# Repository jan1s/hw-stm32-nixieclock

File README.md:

# hw-nixieclock

The firmware running on the clock: [Firmware](https://github.com/jan1s/fw-clock)

A small Gist to configure a STM32 toolchain on Mac: [Toolchain](https://jan1s.github.io)

To flash the controller a STM32 Programmer is needed, just get the cheapest one from China.

## Initial Configuration

Before the clock will actually start working, it is necessary to set the type:

```bash
nixie_settype <type>
nixie_settype <type(0-4)>
```

Where `<type>` is a number defining the nixie clock type.

1. ZM1000
2. Z570M, IN-8
3. ZM1325
4. IN-14, ZM1020

It is also required to set the mode of operation:

```bash
nixie_setmode <mode>
nixie_setmode <mode(0=NONE|1=HHMMSS|2=HHMM|3=MMSS|4=YYYY)>
```

Where `<mode>` is a number defining the nixie operation mode.

1. HH:MM:SS
2. HH:MM
3. MM:SS
4. YYYY

## PCBs

The clock has seperate control and display pcbs. Those pcbs do not only form a basic case for the electronics, but also allow for flexible use with different tubes.

[Control PCBs](layout/control)

[Display PCBs](layout/display)

[Source PCBs](layout/source)

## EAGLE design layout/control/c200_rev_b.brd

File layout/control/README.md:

# Control PCBs

## c100

rev. a

In the first revision of the PCBs are some minor errors. (This is the version from the 32C3 workshop)
Find detailed pictures of the first prototype [here](../../docu/detail_c100_rev_a).

* A pullup resistor is missing on the USB data lines
* LED silkscreen missing, they are on the right of the controller

rev. b

## c150

rev. a

### control BOM
| Identifier | Type/Value | Quantity | [Reichelt][reichelt] | [Digikey][digikey] | Comment |
| :---        | :---        | :---      | :---         | :---      | :---     |
| R1, R2, R3, R4 | 33 Ω | 4 | SMD-0603 33 | 311-33GRCT-ND |
| R12, R13 | 1 kΩ | 2 | SMD-0603 1,00K | 311-1.0KGRCT-ND |
| C1, C2, C13, C14 | 10 pF | 4 | NPO-G0603 10P |  |
| C7, C8 | 10 nF | 2 | X7R-G0603 10N |  |
| C18, C19, C20, C21 | 100 nF | 4 | X7R-G0603 100N |  |
| C3, C5, C6, C10, C11 | 10 µF | 5 | X5R-G0603 10/6 |  |
| FB1 | Ferrite Bead | 1 | BLM18AG 121 | 490-1011-1-ND |
| Y1 | 8MHz | 1 | - | 535-10630-1-ND |
| Y2 | 32kHz | 1 | 32,768 PGD-9 | 535-9542-1-ND |
| LED1 | LED green | 1 | LG L29K |  |
| LED2 | LED white | 1 | LW L283 | |
| BAT1 | Batteryholder | 1 | - | BC501SM-ND | c100 |
| BAT1 | Batteryholder | 1 | KZH 20SMD-2 | - | c150 |
| BAT | CR 1220 | 1 | CR 1220 VAR | SY033-ND |
| SW1 | Tact Switch Top | 1 | - | EG2531CT-ND |
| J1 | 2x5 Socket | 1 | - | A100866TR-ND, S5714-ND |
| J2 | USB Jack | 1 | USB BWM SMD | 151-1206-1-ND |
| IC1 | STM32F103C8T6 | 1 | STM32 F103C8T6 | 497-6063-ND |
| IC2, IC6 | LP2985 | 1 | LP 2985 IM5-3,3 |  |
| IC3, IC4 | USBLC6-2 | 1 | - | 497-5235-1-ND |

### power supply BOM
| Identifier | Type/Value | Quantity | [Reichelt][reichelt] | [Digikey][digikey] | Comment |
| ---        | ---        | ---      | ---         | ---      | ---     |
| R23 | 0.01 Ω | 1 | - | RHM.10MCT-ND |
| R18 | 82 kΩ | 1 | SMD-0603 82K |  |
| R20 | 8,2 kΩ | 1 | SMD-0603 8,2K |  |
| R19 | 1 MΩ | 1 | SMD-1206 1M |  |
| C12 | 150 pF | 1 | NPO-G0603 150P |  |
| C9 | 22 nF | 1 | X7R-G0603 22N |  |
| C4 | 1 µF / 250V | 1 | 1u/250V | 490-3550-1-ND  | |
| C15, C16 | 10 µF | 2 | X5R-G0603 10/6 |  |
| C17 | 100 µF | 1 | X5R-G1210 100 |  |
| D2 | Diode | 1 | BAT 54C SMD |  |
| D3 | Diode | 1 | ES 2GA SMD |  |
| L2 | 680 µH | 1 | L-PISR 680µ |  |
| IC7 | IRF 7470 | 1 | IRF 7470 | IRF7470PBFCT-ND |
| IC5 | LT1619ES8 | 1 | - | LT1619ES8#PBF-ND |

[reichelt]: http://www.reichelt.de
[digikey]: http://www.digikey.de
[mouser]: http://mouser.com
[aliexpress]: http://www.aliexpress.com

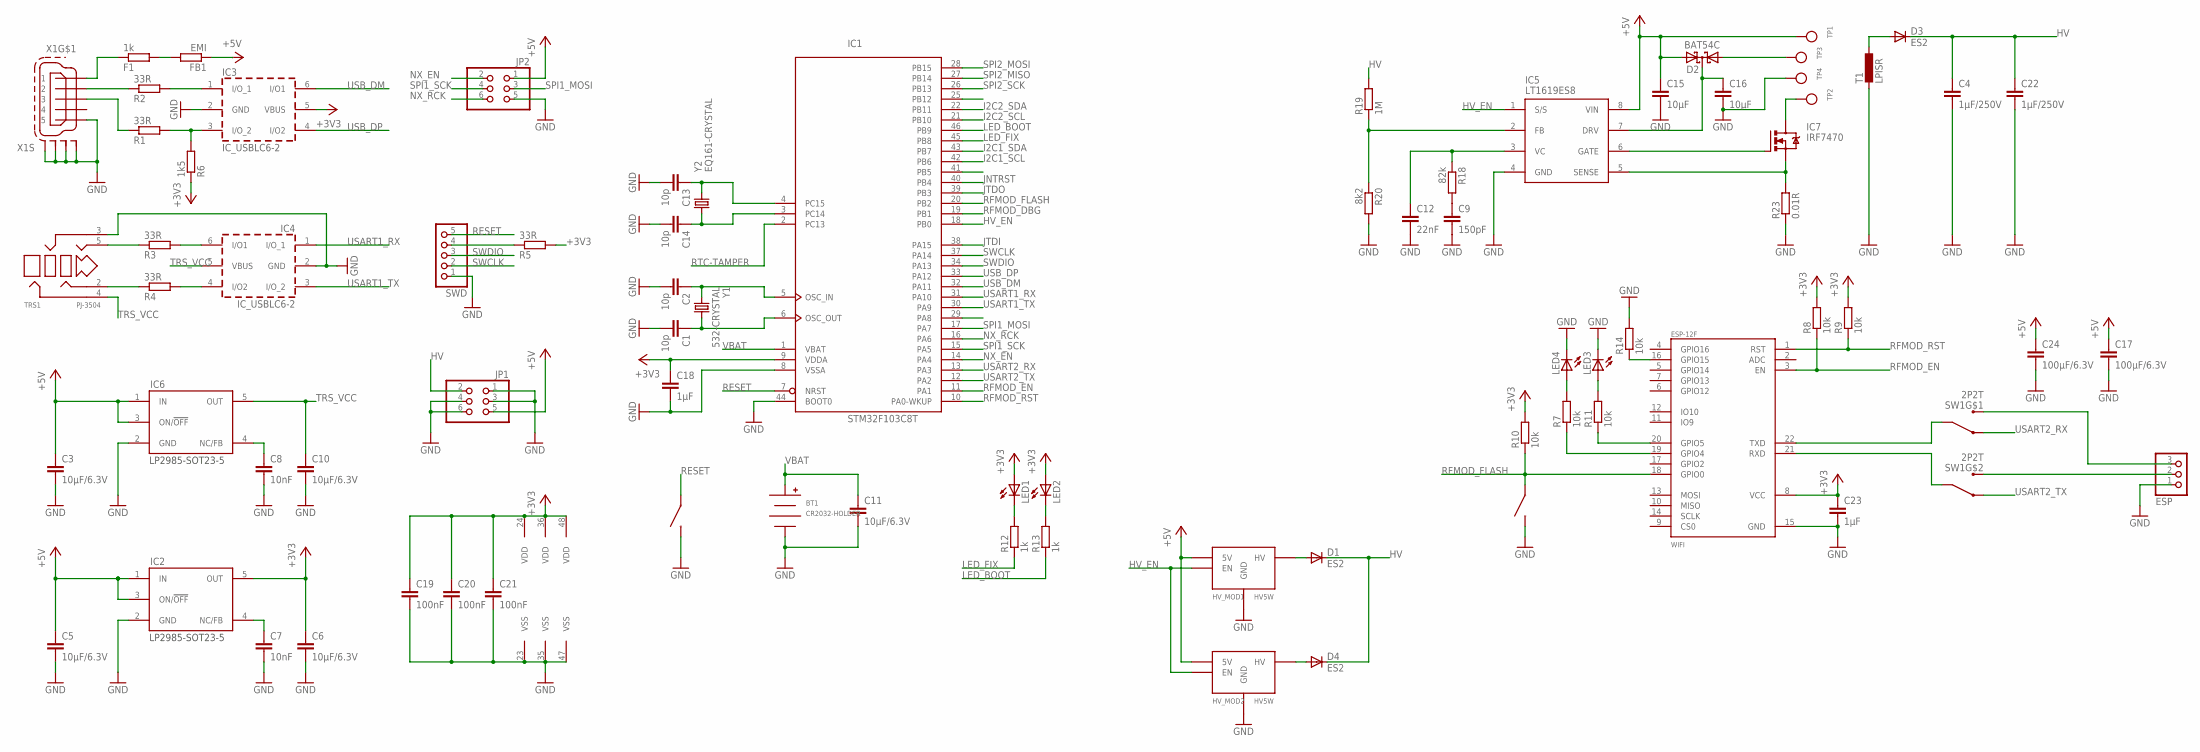
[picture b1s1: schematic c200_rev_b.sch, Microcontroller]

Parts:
BT1: CR2032-HOLDER; CH28-2032LF
C1, C2, C13, C14: 10p; C0603
C3, C5, C6, C10, C11: 10µF/6.3V; C0603
C4, C22: 1µF/250V; C2220K
C7, C8: 10nF; C0603
C9: 150pF; C0603
C12: 22nF; C0603
C15, C16: 10µF; C0603
C17, C24: 100µF/6.3V; C1210
C18, C23: 1µF; C0603
C19, C20, C21: 100nF; C0603
D1, D3, D4: ES2; DO-214AA
D2: BAT54C; SOT23
ESP: HEADER-1X3ROUND; 1X03_ROUND
F1: 1k; R0603
FB1: EMI; R0603
FLASH: TACT-SWITCH-40-40; 40-40
HV_MOD1, HV_MOD2: HV5W; HV5W-D
IC1: STM32F103C8T; LQFP48
IC2, IC6: LP2985-SOT23-5; SOT23-5
IC3, IC4: IC_USBLC6-2; SOT-23-6L
IC5: LT1619ES8; SO8
IC7: IRF7470; SO8
ISP: TACT-SWITCH-40-40; 40-40
JP1, JP2: PINHD-2X3_2.54-SMD; 2X03SMD
LED1, LED2, LED3, LED4: LEDCHIP-LED0603; CHIP-LED0603
R1, R2, R3, R4, R5: 33R; R0603
R6: 1k5; R0603
R7, R8, R9, R10, R11, R14: 10k; R0603
R12, R13: 1k; R0603
R18: 82k; R0603
R19: 1M; M1206
R20: 8k2; R0603
R23: 0.01R; R1206
SW1: 2P2T; MSS22D18
SWD: HEADER-1X5ROUND; 1X05_ROUND
T1: LPISR; PISR
TP1, TP2, TP3, TP4: TESTPOINTROUND2MM; TESTPOINT_ROUND_2MM
TRS1: PJ-3504; YD-PJ-3504
WIFI: ESP-12F
X1: MINI-USB-SCHIELD-32005-201; 32005-201
Y1: 532-CRYSTAL; 2PIN50X32
Y2: EQ161-CRYSTAL; EQ161

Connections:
+3V3: C6.1, C18.1, C19.1, C20.1, C21.1, C23.1, IC1.9 (VDDA), IC1.24 (VDD), IC1.36 (VDD), IC1.48 (VDD), IC2.5 (OUT), IC3.5 (VBUS), LED1.A, LED2.A, R5.2, R6.1, R8.2, R9.2, R10.2, WIFI.8 (VCC)
+5V: C3.1, C5.1, C15.1, C17.1, C24.1, D2.2 (A2), FB1.1, HV_MOD1.+5V (5V), HV_MOD2.+5V (5V), IC2.1 (IN), IC2.3 (ON/!OFF), IC5.8 (VIN), IC6.1 (IN), IC6.3 (ON/!OFF), JP1.5, JP2.1, TP1.P$1
ASDAWJIODJA: R5.1, SWD.4
GND: BT1.NEG, C1.2, C2.2, C3.2, C4.2, C5.2, C6.2, C7.2, C8.2, C9.2, C10.2, C11.2, C12.2, C13.2, C14.2, C15.2, C16.2, C17.2, C18.2, C19.2, C20.2, C21.2, C22.2, C23.2, C24.2, ESP.1, FLASH.1, FLASH.2, HV_MOD1.GND1 (GND), HV_MOD1.GND2 (GND), HV_MOD1.GND3 (GND), HV_MOD2.GND1 (GND), HV_MOD2.GND2 (GND), HV_MOD2.GND3 (GND), IC1.8 (VSSA), IC1.23 (VSS), IC1.35 (VSS), IC1.44 (BOOT0), IC1.47 (VSS), IC2.2 (GND), IC3.2 (GND), IC4.2 (GND), IC5.4 (GND), IC6.2 (GND), ISP.1, ISP.2, JP1.1, JP1.3, JP1.4, JP1.6, JP2.5, LED3.C, LED4.C, R14.2, R20.2, R23.1, SWD.1, T1.P$2 (2), TP4.P$1, TRS1.3, WIFI.15 (GND), X1.5, X1.M1 (S1), X1.M2 (S2), X1.M3 (S3), X1.M4 (S4)
HV: C4.1, C22.1, D1.C, D3.C, D4.C, JP1.2, R19.2
HV_EN: HV_MOD1.EN, HV_MOD2.EN, IC1.18 (PB0), IC5.1 (S/S)
I2C1_SCL: IC1.42 (PB6)
I2C1_SDA: IC1.43 (PB7)
I2C2_SCL: IC1.21 (PB10)
I2C2_SDA: IC1.22 (PB11)
JNTRST: IC1.40 (PB4)
JTDI: IC1.38 (PA15)
JTDO: IC1.39 (PB3)
LED_BOOT: IC1.46 (PB9), R13.1
LED_FIX: IC1.45 (PB8), R12.1
unnamed: C1.1, IC1.6 (OSC_OUT), Y1.P$1 (1)
unnamed: C2.1, IC1.5 (OSC_IN), Y1.P$2 (2)
unnamed: F1.1, X1.1
unnamed: C8.1, IC6.4 (NC/FB)
unnamed: IC3.3 (I/O_2), R1.2, R6.2
unnamed: R14.1, WIFI.16 (GPIO15)
unnamed: IC4.6 (I/O1), R3.2
unnamed: D2.1 (A1), TP3.P$1
unnamed: IC5.6 (GATE), IC7.4 (G)
unnamed: LED2.C, R13.2
unnamed: LED1.C, R12.2
unnamed: R4.1, TRS1.2
unnamed: IC7.5 (D), IC7.6 (D), IC7.7 (D), IC7.8 (D), TP2.P$1
unnamed: C12.1, IC5.3 (VC), R18.1
unnamed: C9.1, R18.2
unnamed: D3.A, T1.P$1 (1)
unnamed: IC5.2 (FB), R19.1, R20.1
unnamed: IC5.5 (SENSE), IC7.1 (S), IC7.2 (S), IC7.3 (S), R23.2
unnamed: C16.1, D2.3 (CC), IC5.7 (DRV)
unnamed: C7.1, IC2.4 (NC/FB)
unnamed: SW1.C1 (C), WIFI.22 (TXD)
unnamed: F1.2, FB1.2
unnamed: IC3.1 (I/O_1), R2.2
unnamed: R2.1, X1.2
unnamed: IC4.4 (I/O2), R4.2
unnamed: SW1.C2 (C), WIFI.21 (RXD)
unnamed: R11.1, WIFI.20 (GPIO5)
unnamed: R3.1, TRS1.5
unnamed: C13.1, IC1.4 (PC15), Y2.P$1 (1)
unnamed: C14.1, IC1.3 (PC14), Y2.P$2 (2)
unnamed: ESP.3, SW1.B1 (B)
unnamed: ESP.2, SW1.B2 (B)
unnamed: R7.1, WIFI.19 (GPIO4)
unnamed: LED4.A, R7.2
unnamed: LED3.A, R11.2
unnamed: R1.1, X1.3
unnamed: D1.A, HV_MOD1.HV
unnamed: D4.A, HV_MOD2.HV
NX_EN: IC1.14 (PA4), JP2.2
NX_RCK: IC1.16 (PA6), JP2.6
RESET: IC1.7 (NRST), ISP.3, ISP.4, SWD.5
RFMOD_DBG: IC1.19 (PB1)
RFMOD_EN: IC1.11 (PA1), R8.1, WIFI.3 (EN)
RFMOD_FLASH: FLASH.3, FLASH.4, IC1.20 (PB2), R10.1, WIFI.18 (GPIO0)
RFMOD_RST: IC1.10 (PA0-WKUP), R9.1, WIFI.1 (RST)
RTC-TAMPER: IC1.2 (PC13)
SPI1_MOSI: IC1.17 (PA7), JP2.3
SPI1_SCK: IC1.15 (PA5), JP2.4
SPI2_MISO: IC1.27 (PB14)
SPI2_MOSI: IC1.28 (PB15)
SPI2_SCK: IC1.26 (PB13)
SWCLK: IC1.37 (PA14), SWD.2
SWDIO: IC1.34 (PA13), SWD.3
TRS_VCC: C10.1, IC4.5 (VBUS), IC6.5 (OUT), TRS1.4
USART1_RX: IC1.31 (PA10), IC4.1 (I/O_1)
USART1_TX: IC1.30 (PA9), IC4.3 (I/O_2)
USART2_RX: IC1.13 (PA3), SW1.A1 (A)
USART2_TX: IC1.12 (PA2), SW1.A2 (A)
USB_DM: IC1.32 (PA11), IC3.6 (I/O1)
USB_DP: IC1.33 (PA12), IC3.4 (I/O2)
VBAT: BT1.POS, C11.1, IC1.1 (VBAT)

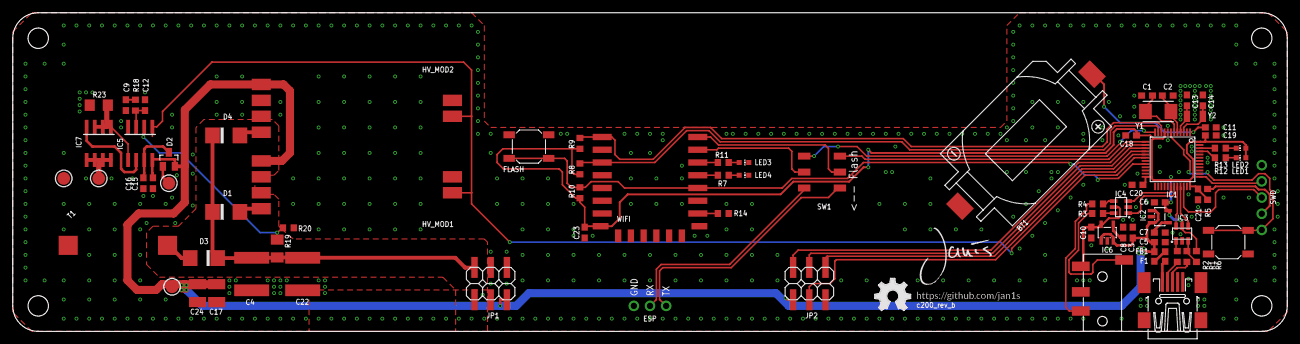
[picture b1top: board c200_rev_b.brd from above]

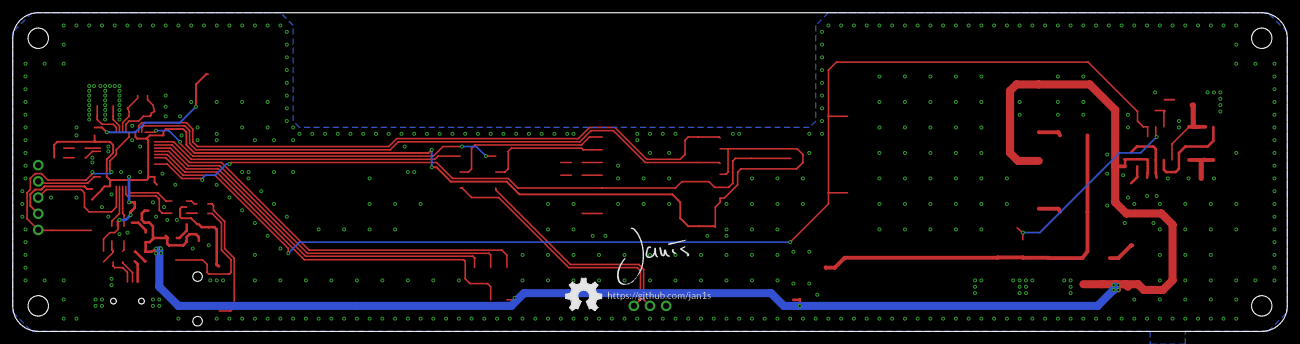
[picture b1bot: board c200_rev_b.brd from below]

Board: 2 copper layers, 200.0 x 50.0 mm, 85 parts (3 on the bottom side), 64 nets.

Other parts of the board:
LOGO1, LOGO2: OSHW_LOGO_FILLX0200-NT; OSHW_FILLX200_NOTEXT
U$1, U$2: JANIS_10MM
U$5, U$6: GITHUB/JAN1S

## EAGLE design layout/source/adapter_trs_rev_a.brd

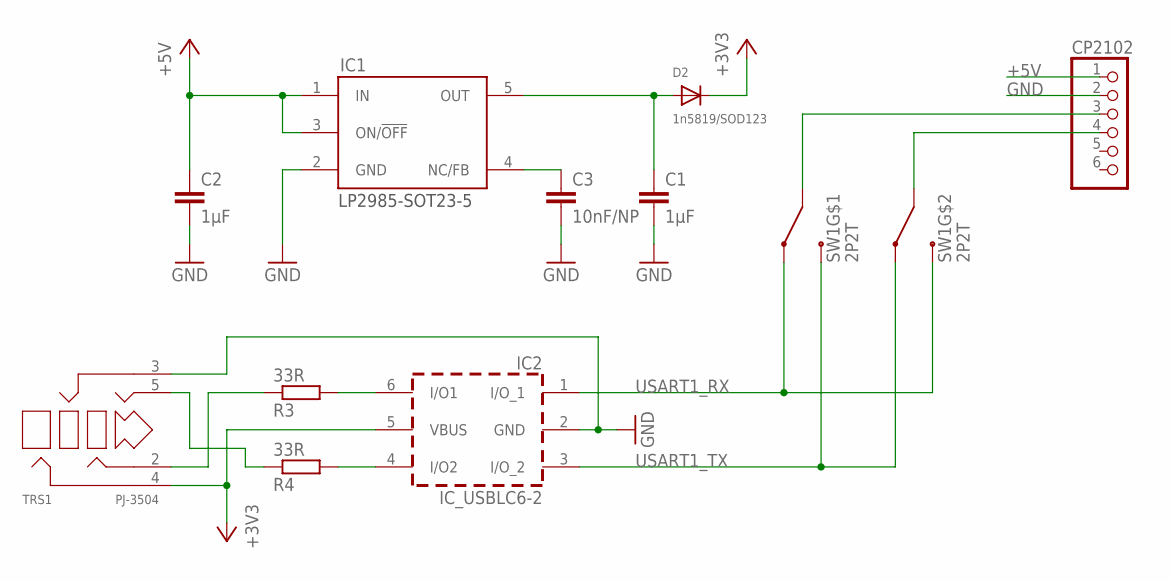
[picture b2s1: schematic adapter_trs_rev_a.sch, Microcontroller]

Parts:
C1, C2: 1µF; C0603
C3: 10nF/NP; C0603
CP2102: HEADER-1X6ROUND; 1X06_ROUND
D2: 1n5819/SOD123; SOD-123
IC1: LP2985-SOT23-5; SOT23-5
IC2: IC_USBLC6-2; SOT-23-6L
R3, R4: 33R; R0603
SW1: 2P2T; MSS22D18
TRS1: PJ-3504; YD-PJ-3504

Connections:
+3V3: D2.C, IC2.5 (VBUS), TRS1.4
+5V: C2.1, CP2102.1, IC1.1 (IN), IC1.3 (ON/!OFF)
GND: C1.2, C2.2, C3.2, CP2102.2, IC1.2 (GND), IC2.2 (GND), TRS1.3
unnamed: C1.1, D2.A, IC1.5 (OUT)
unnamed: C3.1, IC1.4 (NC/FB)
unnamed: R3.1, TRS1.2
unnamed: CP2102.3, SW1.C1 (C)
unnamed: IC2.6 (I/O1), R3.2
unnamed: R4.1, TRS1.5
unnamed: CP2102.4, SW1.C2 (C)
unnamed: IC2.4 (I/O2), R4.2
USART1_RX: IC2.1 (I/O_1), SW1.A1 (A), SW1.B2 (B)
USART1_TX: IC2.3 (I/O_2), SW1.A2 (A), SW1.B1 (B)

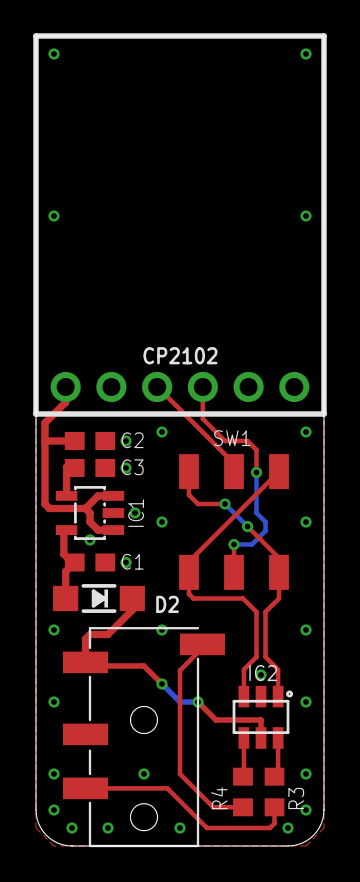
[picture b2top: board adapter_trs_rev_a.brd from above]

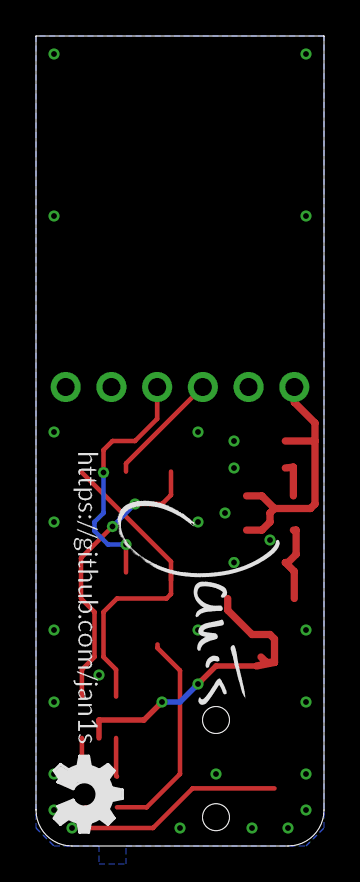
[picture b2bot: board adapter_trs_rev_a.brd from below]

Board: 2 copper layers, 16.0 x 45.0 mm, 14 parts (3 on the bottom side), 13 nets.

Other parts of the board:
U$1: OSHW_FILLX150_NOTEXT
U$2: JANIS_10MM
U$6: GITHUB/JAN1S

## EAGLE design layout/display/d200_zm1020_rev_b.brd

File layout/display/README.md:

# Display PCBs

## d100

The display boards with 100mm width use a smaller variant of the 74hc595 shift register.

### d100 ZM1000

rev. a

In rev a of the PCB is an error. (This is the version from the 32C3 workshop)
Find detailed pictures of the first prototype [here](../../docu/detail_d100_zm1325_rev_a).

* SCL of the shift registers are floating, they need to be connected to 5V

rev. b

### d100 ZM1325

rev. a

In rev a of the PCB is an error. (This is the version from the 32C3 workshop)

* SCL of the shift registers are floating, they need to be connected to 5V

rev. b

### d100 BOM

| Identifier | Type/Value | Quantity | [Reichelt][reichelt] | [Digikey][digikey] | Comment |
| ---        | ---        | ---      | ---         | ---      | ---     |
| R1-R2 | 220 kΩ | 2 | SMD-0603 220K |  |
| R10-R46 | 22 kΩ | 4 | SMD-0603 22K |  |
| RN10-RN61| 4x10 kΩ | 12 | BCN16 10K |  |
| C1-C6 | 100 nF | 6 | X7R-G0603 100N |  |
| T1-T69 | SMBTA 42 SMD | 46 | SMBTA 42 SMD | SMBTA42E6327INCT-ND |
| IC1-IC6 | 74HC595PW | 6 |  | 568-2263-1-ND |
| JP1 | 2x5pol Header | 1 | SL 2X10G SMD2,54 | 609-4723-ND |
| GL1, GL2 | Neon Bulb | 2 | GLIMMLAMPE | C2A-ND |

##d150

The display boards with 150mm width use 8 74hc595d shift registers.

### d150 ZM1000

rev. a

rev. a, socketed

### d150 Z570M

rev. a

rev. b

### d150 IN-8

rev. a

rev. b

### d150 IN-8-2

rev. a

### d150 IN-14

rev. a

rev. b

### d150 BOM

| Identifier | Type/Value | Quantity | [Reichelt][reichelt] | [Digikey][digikey] | Comment |
| ---        | ---        | ---      | ---         | ---      | ---     |
| R1-R4 | 220 kΩ | 4 | SMD-0603 220K |  |
| R10-R60 | 22 kΩ | 6 | SMD-0603 22K |  |
| RN10-RN81| 4x10 kΩ | 16 | BCN16 10K |  |
| C1-C8 | 100 nF | 8 | X7R-G0603 100N |  |
| T1-T69 | SMBTA 42 SMD | 64 | SMBTA 42 SMD | SMBTA42E6327INCT-ND |
| IC1-IC8 | 74HC595D | 8 | SMD HC 595 | |
| JP1, JP2 | 2x3pol Header | 2 | SL 2X10G SMD2,54 | |
| GL1-GL4 | Neon Bulb | 4 | GLIMMLAMPE | C2A-ND |

[reichelt]: http://www.reichelt.de
[digikey]: http://www.digikey.de
[mouser]: http://mouser.com
[aliexpress]: http://www.aliexpress.com

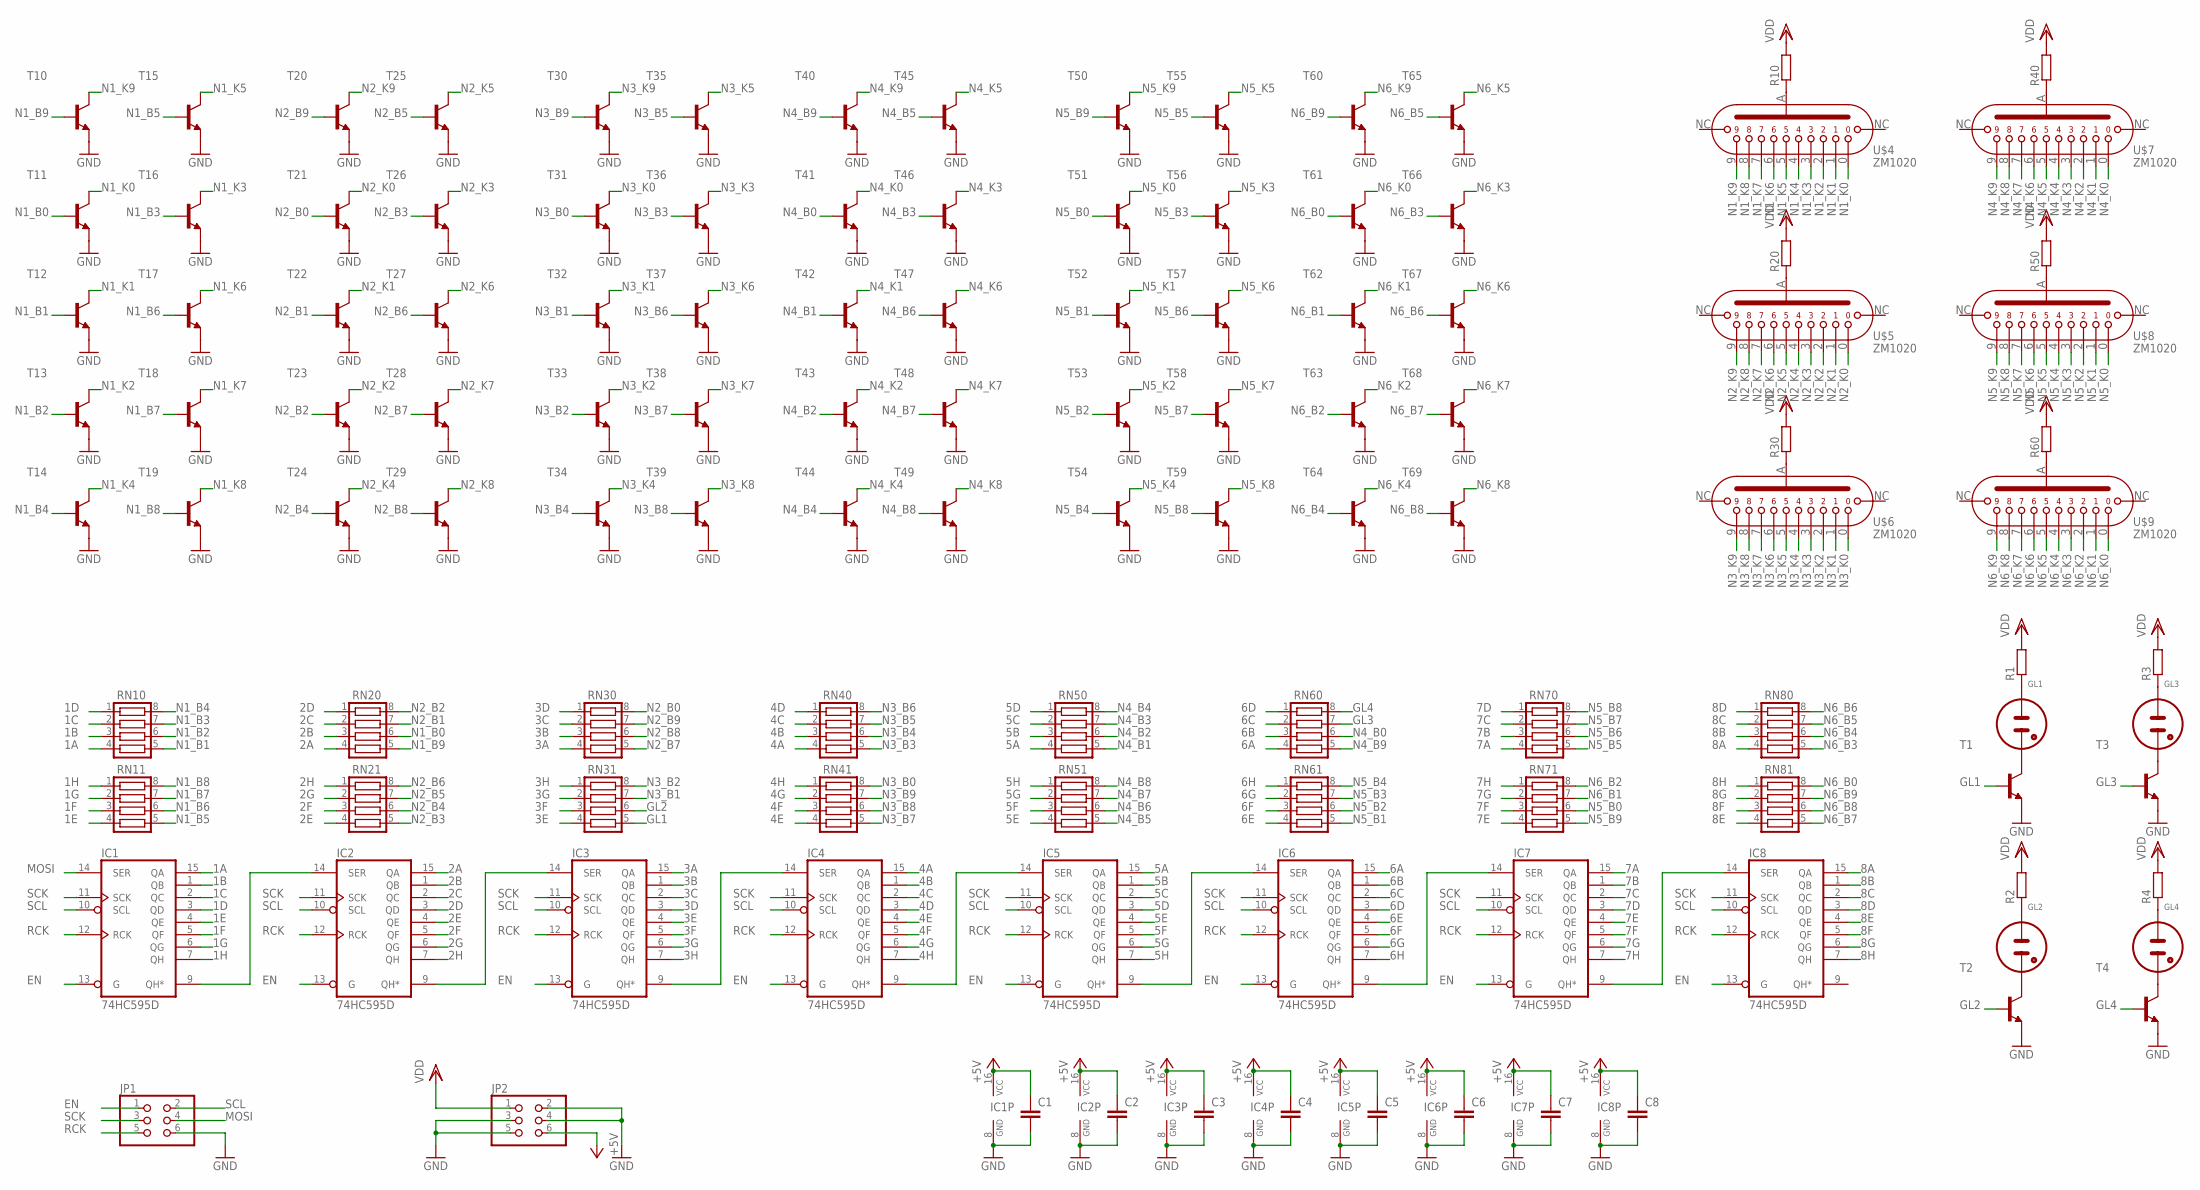
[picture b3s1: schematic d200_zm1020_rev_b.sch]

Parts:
C1, C2, C3, C4, C5, C6, C7, C8: C-EUC0603; C0603
GL1, GL2, GL3, GL4: NE2-NEON-BULB-DRILL
IC1, IC2, IC3, IC4, IC5, IC6, IC7, IC8: 74HC595D; SO16
JP1, JP2: PINHD-2X3_2.54-SMD; 2X03SMD
R1, R2, R3, R4, R10, R20, R30, R40, R50, R60: R-EU_R0603; R0603
RN10, RN11, RN20, RN21, RN30, RN31, RN40, RN41, RN50, RN51, RN60, RN61, RN70, RN71, RN80, RN81: CTS742C083
T1, T2, T3, T4, T10, T11, T12, T13, T14, T15, T16, T17, T18, T19, T20, T21, T22, T23, T24, T25, T26, T27, T28, T29, T30, T31, T32, T33, T34, T35, T36, T37, T38, T39, T40, T41, T42, T43, T44, T45, T46, T47, T48, T49, T50, T51, T52, T53, T54, T55, T56, T57, T58, T59, T60, T61, T62, T63, T64, T65, T66, T67, T68, T69: SMBTA42; SOT23
U$4, U$5, U$6, U$7, U$8, U$9: ZM1020

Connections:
1A: IC1.15 (QA), RN10.4
1B: IC1.1 (QB), RN10.3
1C: IC1.2 (QC), RN10.2
1D: IC1.3 (QD), RN10.1
1E: IC1.4 (QE), RN11.4
1F: IC1.5 (QF), RN11.3
1G: IC1.6 (QG), RN11.2
1H: IC1.7 (QH), RN11.1
2A: IC2.15 (QA), RN20.4
2B: IC2.1 (QB), RN20.3
2C: IC2.2 (QC), RN20.2
2D: IC2.3 (QD), RN20.1
2E: IC2.4 (QE), RN21.4
2F: IC2.5 (QF), RN21.3
2G: IC2.6 (QG), RN21.2
2H: IC2.7 (QH), RN21.1
3A: IC3.15 (QA), RN30.4
3B: IC3.1 (QB), RN30.3
3C: IC3.2 (QC), RN30.2
3D: IC3.3 (QD), RN30.1
3E: IC3.4 (QE), RN31.4
3F: IC3.5 (QF), RN31.3
3G: IC3.6 (QG), RN31.2
3H: IC3.7 (QH), RN31.1
4A: IC4.15 (QA), RN40.4
4B: IC4.1 (QB), RN40.3
4C: IC4.2 (QC), RN40.2
4D: IC4.3 (QD), RN40.1
4E: IC4.4 (QE), RN41.4
4F: IC4.5 (QF), RN41.3
4G: IC4.6 (QG), RN41.2
4H: IC4.7 (QH), RN41.1
5A: IC5.15 (QA), RN50.4
5B: IC5.1 (QB), RN50.3
5C: IC5.2 (QC), RN50.2
5D: IC5.3 (QD), RN50.1
5E: IC5.4 (QE), RN51.4
5F: IC5.5 (QF), RN51.3
5G: IC5.6 (QG), RN51.2
5H: IC5.7 (QH), RN51.1
6A: IC6.15 (QA), RN60.4
6B: IC6.1 (QB), RN60.3
6C: IC6.2 (QC), RN60.2
6D: IC6.3 (QD), RN60.1
6E: IC6.4 (QE), RN61.4
6F: IC6.5 (QF), RN61.3
6G: IC6.6 (QG), RN61.2
6H: IC6.7 (QH), RN61.1
7A: IC7.15 (QA), RN70.4
7B: IC7.1 (QB), RN70.3
7C: IC7.2 (QC), RN70.2
7D: IC7.3 (QD), RN70.1
7E: IC7.4 (QE), RN71.4
7F: IC7.5 (QF), RN71.3
7G: IC7.6 (QG), RN71.2
7H: IC7.7 (QH), RN71.1
8A: IC8.15 (QA), RN80.4
8B: IC8.1 (QB), RN80.3
8C: IC8.2 (QC), RN80.2
8D: IC8.3 (QD), RN80.1
8E: IC8.4 (QE), RN81.4
8F: IC8.5 (QF), RN81.3
8G: IC8.6 (QG), RN81.2
8H: IC8.7 (QH), RN81.1
+5V: C1.1, C2.1, C3.1, C4.1, C5.1, C6.1, C7.1, C8.1, IC1.16 (VCC), IC2.16 (VCC), IC3.16 (VCC), IC4.16 (VCC), IC5.16 (VCC), IC6.16 (VCC), IC7.16 (VCC), IC8.16 (VCC), JP2.6
EN: IC1.13 (G), IC2.13 (G), IC3.13 (G), IC4.13 (G), IC5.13 (G), IC6.13 (G), IC7.13 (G), IC8.13 (G), JP1.1
GL1: RN31.5, T1.1 (B)
GL2: RN31.6, T2.1 (B)
GL3: RN60.7, T3.1 (B)
GL4: RN60.8, T4.1 (B)
GND: C1.2, C2.2, C3.2, C4.2, C5.2, C6.2, C7.2, C8.2, IC1.8 (GND), IC2.8 (GND), IC3.8 (GND), IC4.8 (GND), IC5.8 (GND), IC6.8 (GND), IC7.8 (GND), IC8.8 (GND), JP1.6, JP2.2, JP2.3, JP2.4, JP2.5, T1.2 (E), T2.2 (E), T3.2 (E), T4.2 (E), T10.2 (E), T11.2 (E), T12.2 (E), T13.2 (E), T14.2 (E), T15.2 (E), T16.2 (E), T17.2 (E), T18.2 (E), T19.2 (E), T20.2 (E), T21.2 (E), T22.2 (E), T23.2 (E), T24.2 (E), T25.2 (E), T26.2 (E), T27.2 (E), T28.2 (E), T29.2 (E), T30.2 (E), T31.2 (E), T32.2 (E), T33.2 (E), T34.2 (E), T35.2 (E), T36.2 (E), T37.2 (E), T38.2 (E), T39.2 (E), T40.2 (E), T41.2 (E), T42.2 (E), T43.2 (E), T44.2 (E), T45.2 (E), T46.2 (E), T47.2 (E), T48.2 (E), T49.2 (E), T50.2 (E), T51.2 (E), T52.2 (E), T53.2 (E), T54.2 (E), T55.2 (E), T56.2 (E), T57.2 (E), T58.2 (E), T59.2 (E), T60.2 (E), T61.2 (E), T62.2 (E), T63.2 (E), T64.2 (E), T65.2 (E), T66.2 (E), T67.2 (E), T68.2 (E), T69.2 (E)
MOSI: IC1.14 (SER), JP1.4
N1_B0: RN20.6, T11.1 (B)
N1_B1: RN10.5, T12.1 (B)
N1_B2: RN10.6, T13.1 (B)
N1_B3: RN10.7, T16.1 (B)
N1_B4: RN10.8, T14.1 (B)
N1_B5: RN11.5, T15.1 (B)
N1_B6: RN11.6, T17.1 (B)
N1_B7: RN11.7, T18.1 (B)
N1_B8: RN11.8, T19.1 (B)
N1_B9: RN20.5, T10.1 (B)
N1_K0: T11.3 (C), U$4.P3 (0)
N1_K1: T12.3 (C), U$4.P13 (1)
N1_K2: T13.3 (C), U$4.P12 (2)
N1_K3: T16.3 (C), U$4.P11 (3)
N1_K4: T14.3 (C), U$4.P10 (4)
N1_K5: T15.3 (C), U$4.P9 (5)
N1_K6: T17.3 (C), U$4.P7 (6)
N1_K7: T18.3 (C), U$4.P6 (7)
N1_K8: T19.3 (C), U$4.P5 (8)
N1_K9: T10.3 (C), U$4.P4 (9)
N2_B0: RN30.8, T21.1 (B)
N2_B1: RN20.7, T22.1 (B)
N2_B2: RN20.8, T23.1 (B)
N2_B3: RN21.5, T26.1 (B)
N2_B4: RN21.6, T24.1 (B)
N2_B5: RN21.7, T25.1 (B)
N2_B6: RN21.8, T27.1 (B)
N2_B7: RN30.5, T28.1 (B)
N2_B8: RN30.6, T29.1 (B)
N2_B9: RN30.7, T20.1 (B)
N2_K0: T21.3 (C), U$5.P3 (0)
N2_K1: T22.3 (C), U$5.P13 (1)
N2_K2: T23.3 (C), U$5.P12 (2)
N2_K3: T26.3 (C), U$5.P11 (3)
N2_K4: T24.3 (C), U$5.P10 (4)
N2_K5: T25.3 (C), U$5.P9 (5)
N2_K6: T27.3 (C), U$5.P7 (6)
N2_K7: T28.3 (C), U$5.P6 (7)
N2_K8: T29.3 (C), U$5.P5 (8)
N2_K9: T20.3 (C), U$5.P4 (9)
N3_B0: RN41.8, T31.1 (B)
N3_B1: RN31.7, T32.1 (B)
N3_B2: RN31.8, T33.1 (B)
N3_B3: RN40.5, T36.1 (B)
N3_B4: RN40.6, T34.1 (B)
N3_B5: RN40.7, T35.1 (B)
N3_B6: RN40.8, T37.1 (B)
N3_B7: RN41.5, T38.1 (B)
N3_B8: RN41.6, T39.1 (B)
N3_B9: RN41.7, T30.1 (B)
N3_K0: T31.3 (C), U$6.P3 (0)
N3_K1: T32.3 (C), U$6.P13 (1)
N3_K2: T33.3 (C), U$6.P12 (2)
N3_K3: T36.3 (C), U$6.P11 (3)
N3_K4: T34.3 (C), U$6.P10 (4)
N3_K5: T35.3 (C), U$6.P9 (5)
N3_K6: T37.3 (C), U$6.P7 (6)
N3_K7: T38.3 (C), U$6.P6 (7)
N3_K8: T39.3 (C), U$6.P5 (8)
N3_K9: T30.3 (C), U$6.P4 (9)
N4_B0: RN60.6, T41.1 (B)
N4_B1: RN50.5, T42.1 (B)
N4_B2: RN50.6, T43.1 (B)
N4_B3: RN50.7, T46.1 (B)
N4_B4: RN50.8, T44.1 (B)
N4_B5: RN51.5, T45.1 (B)
N4_B6: RN51.6, T47.1 (B)
N4_B7: RN51.7, T48.1 (B)
N4_B8: RN51.8, T49.1 (B)
N4_B9: RN60.5, T40.1 (B)
N4_K0: T41.3 (C), U$7.P3 (0)
N4_K1: T42.3 (C), U$7.P13 (1)
N4_K2: T43.3 (C), U$7.P12 (2)
N4_K3: T46.3 (C), U$7.P11 (3)
N4_K4: T44.3 (C), U$7.P10 (4)
N4_K5: T45.3 (C), U$7.P9 (5)
N4_K6: T47.3 (C), U$7.P7 (6)
N4_K7: T48.3 (C), U$7.P6 (7)
N4_K8: T49.3 (C), U$7.P5 (8)
N4_K9: T40.3 (C), U$7.P4 (9)
N5_B0: RN71.6, T51.1 (B)
N5_B1: RN61.5, T52.1 (B)
N5_B2: RN61.6, T53.1 (B)
N5_B3: RN61.7, T56.1 (B)
N5_B4: RN61.8, T54.1 (B)
N5_B5: RN70.5, T55.1 (B)
N5_B6: RN70.6, T57.1 (B)
N5_B7: RN70.7, T58.1 (B)
N5_B8: RN70.8, T59.1 (B)
N5_B9: RN71.5, T50.1 (B)
N5_K0: T51.3 (C), U$8.P3 (0)
N5_K1: T52.3 (C), U$8.P13 (1)
N5_K2: T53.3 (C), U$8.P12 (2)
N5_K3: T56.3 (C), U$8.P11 (3)
N5_K4: T54.3 (C), U$8.P10 (4)
N5_K5: T55.3 (C), U$8.P9 (5)
N5_K6: T57.3 (C), U$8.P7 (6)
N5_K7: T58.3 (C), U$8.P6 (7)
N5_K8: T59.3 (C), U$8.P5 (8)
N5_K9: T50.3 (C), U$8.P4 (9)
N6_B0: RN81.8, T61.1 (B)
N6_B1: RN71.7, T62.1 (B)
N6_B2: RN71.8, T63.1 (B)
N6_B3: RN80.5, T66.1 (B)
N6_B4: RN80.6, T64.1 (B)
N6_B5: RN80.7, T65.1 (B)
N6_B6: RN80.8, T67.1 (B)
N6_B7: RN81.5, T68.1 (B)
N6_B8: RN81.6, T69.1 (B)
N6_B9: RN81.7, T60.1 (B)
N6_K0: T61.3 (C), U$9.P3 (0)
N6_K1: T62.3 (C), U$9.P13 (1)
N6_K2: T63.3 (C), U$9.P12 (2)
N6_K3: T66.3 (C), U$9.P11 (3)
N6_K4: T64.3 (C), U$9.P10 (4)
N6_K5: T65.3 (C), U$9.P9 (5)
N6_K6: T67.3 (C), U$9.P7 (6)
N6_K7: T68.3 (C), U$9.P6 (7)
N6_K8: T69.3 (C), U$9.P5 (8)
N6_K9: T60.3 (C), U$9.P4 (9)
unnamed: GL2.1 (A), R2.1
unnamed: GL3.1 (A), R3.1
unnamed: GL4.1 (A), R4.1
unnamed: R10.1, U$4.P2 (A)
unnamed: GL2.2 (A1), T2.3 (C)
unnamed: GL1.2 (A1), T1.3 (C)
unnamed: GL4.2 (A1), T4.3 (C)
unnamed: GL3.2 (A1), T3.3 (C)
unnamed: R20.1, U$5.P2 (A)
unnamed: IC1.9 (QH*), IC2.14 (SER)
unnamed: IC2.9 (QH*), IC3.14 (SER)
unnamed: IC3.9 (QH*), IC4.14 (SER)
unnamed: R30.1, U$6.P2 (A)
unnamed: R40.1, U$7.P2 (A)
unnamed: R50.1, U$8.P2 (A)
unnamed: IC4.9 (QH*), IC5.14 (SER)
unnamed: R60.1, U$9.P2 (A)
unnamed: IC5.9 (QH*), IC6.14 (SER)
unnamed: IC6.9 (QH*), IC7.14 (SER)
unnamed: IC7.9 (QH*), IC8.14 (SER)
unnamed: GL1.1 (A), R1.1
RCK: IC1.12 (RCK), IC2.12 (RCK), IC3.12 (RCK), IC4.12 (RCK), IC5.12 (RCK), IC6.12 (RCK), IC7.12 (RCK), IC8.12 (RCK), JP1.5
SCK: IC1.11 (SCK), IC2.11 (SCK), IC3.11 (SCK), IC4.11 (SCK), IC5.11 (SCK), IC6.11 (SCK), IC7.11 (SCK), IC8.11 (SCK), JP1.3
SCL: IC1.10 (SCL), IC2.10 (SCL), IC3.10 (SCL), IC4.10 (SCL), IC5.10 (SCL), IC6.10 (SCL), IC7.10 (SCL), IC8.10 (SCL), JP1.2
VDD: JP2.1, R1.2, R2.2, R3.2, R4.2, R10.2, R20.2, R30.2, R40.2, R50.2, R60.2

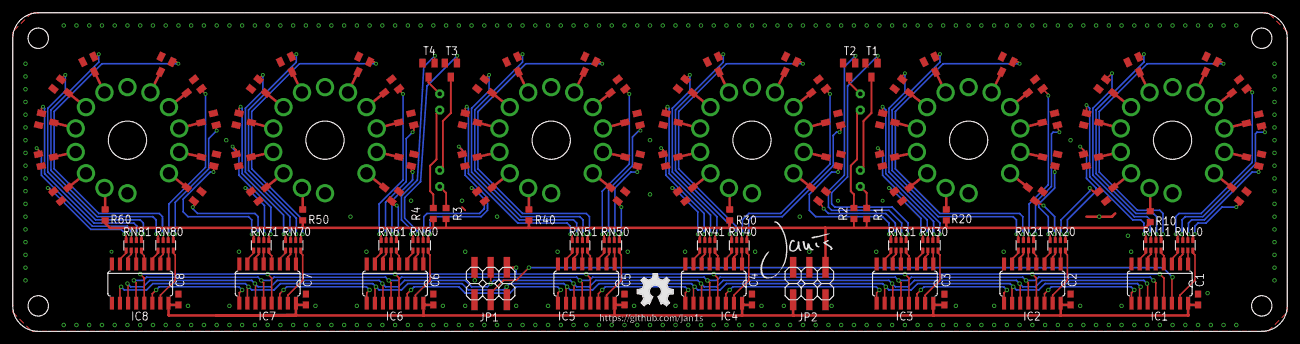
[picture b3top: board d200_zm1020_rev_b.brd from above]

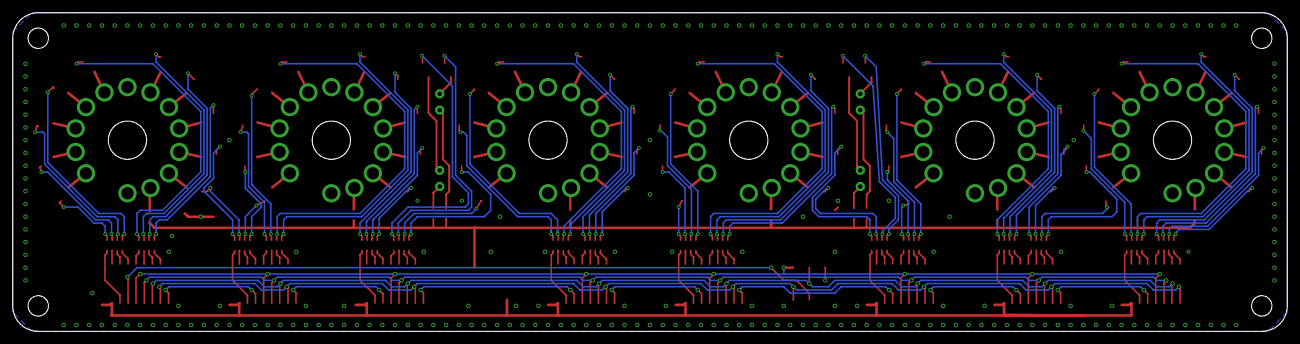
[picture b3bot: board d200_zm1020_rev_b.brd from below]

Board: 2 copper layers, 200.0 x 50.0 mm, 121 parts (10 on the bottom side), 217 nets.

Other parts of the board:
U$1: OSHW_FILLX200_NOTEXT
U$2: JANIS_10MM
U$3: GITHUB/JAN1S

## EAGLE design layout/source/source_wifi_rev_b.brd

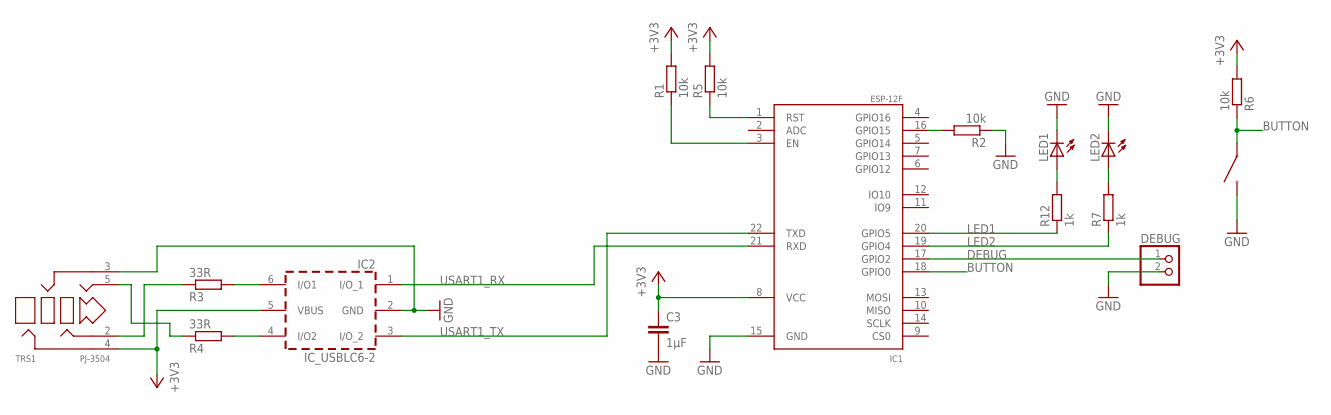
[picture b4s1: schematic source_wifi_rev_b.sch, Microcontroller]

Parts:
C3: 1µF; C0603
DEBUG: HEADER-1X2ROUND; 1X02_ROUND
IC1: ESP-12F
IC2: IC_USBLC6-2; SOT-23-6L
ISP: TACT-SWITCH-40-40; 40-40
LED1, LED2: LEDCHIP-LED0603; CHIP-LED0603
R1, R2, R5, R6: 10k; R0603
R3, R4: 33R; R0603
R7, R12: 1k; R0603
TRS1: PJ-3504; YD-PJ-3504

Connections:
+3V3: C3.1, IC1.8 (VCC), IC2.5 (VBUS), R1.2, R5.2, R6.2, TRS1.4
BUTTON: IC1.18 (GPIO0), ISP.3, ISP.4, R6.1
DEBUG: DEBUG.1, IC1.17 (GPIO2)
GND: C3.2, DEBUG.2, IC1.15 (GND), IC2.2 (GND), ISP.1, ISP.2, LED1.C, LED2.C, R2.1, TRS1.3
LED1: IC1.20 (GPIO5), R12.1
LED2: IC1.19 (GPIO4), R7.1
unnamed: IC1.3 (EN), R1.1
unnamed: IC1.16 (GPIO15), R2.2
unnamed: IC1.1 (RST), R5.1
unnamed: R3.1, TRS1.2
unnamed: LED2.A, R7.2
unnamed: LED1.A, R12.2
unnamed: IC2.6 (I/O1), R3.2
unnamed: R4.1, TRS1.5
unnamed: IC2.4 (I/O2), R4.2
USART1_RX: IC1.21 (RXD), IC2.1 (I/O_1)
USART1_TX: IC1.22 (TXD), IC2.3 (I/O_2)

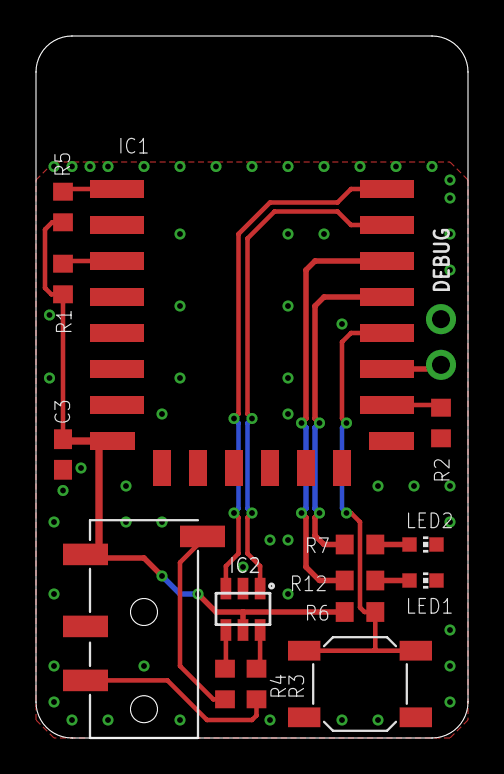
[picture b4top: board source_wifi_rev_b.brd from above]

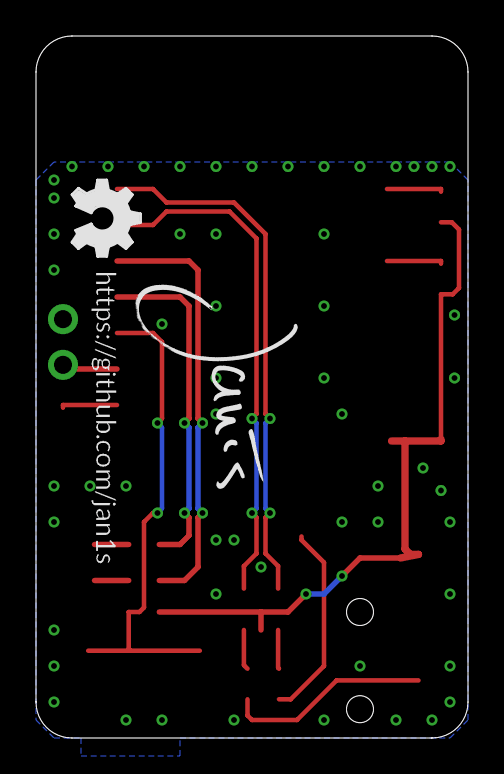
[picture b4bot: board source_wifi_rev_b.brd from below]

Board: 2 copper layers, 24.0 x 39.0 mm, 19 parts (3 on the bottom side), 17 nets.

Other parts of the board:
U$1: OSHW_FILLX150_NOTEXT
U$2: JANIS_10MM
U$6: GITHUB/JAN1S

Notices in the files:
parts and their libraries:
microbuilder: This work is placed in the public domain, and may be freely used for commercial and non-commercial work with the following conditions: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
